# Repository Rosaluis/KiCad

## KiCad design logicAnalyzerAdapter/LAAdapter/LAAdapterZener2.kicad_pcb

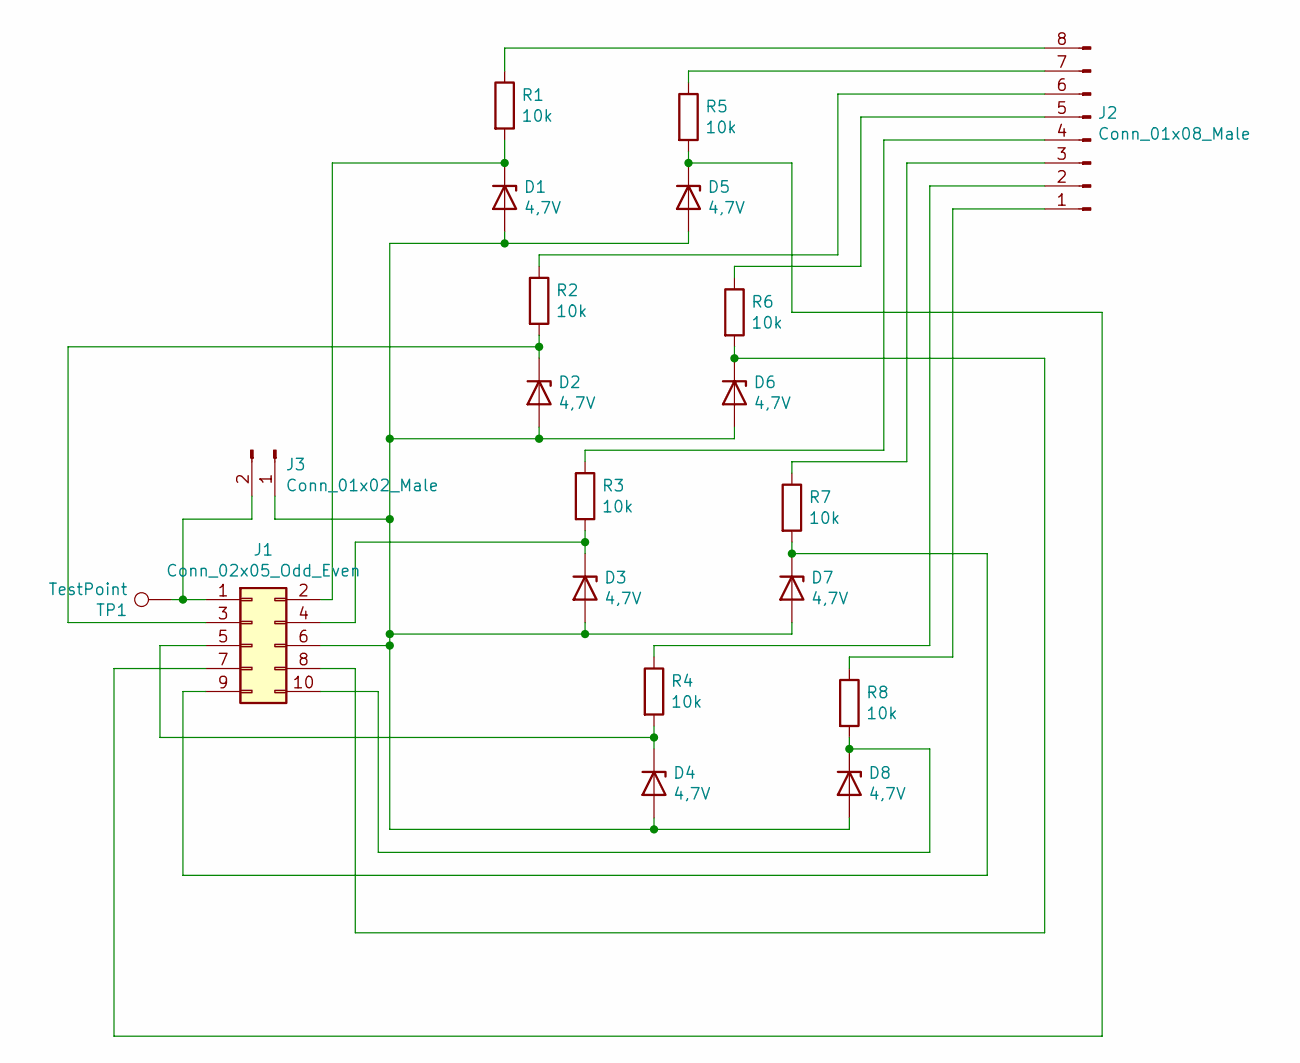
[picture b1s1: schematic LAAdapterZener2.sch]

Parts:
D1, D2, D3, D4, D5, D6, D7, D8: 4,7V; AR_D_DO-34_SOD68_P7.62mm_Horizontal
J1: Conn_02x05_Odd_Even; AR_PinHeader_2x05_P2.54mm_Horizontal_2
J2: Conn_01x08_Male; AR_PinHeader_1x08_P2.54mm_Vertical
J3: Conn_01x02_Male; SolderJumper-2_P1.3mm_Open_TrianglePad1.0x1.5mm
R1, R2, R3, R4, R5, R6, R7, R8: 10k; AR_R_0805_2012Metric
TP1: TestPoint; AR_PinHeader_1x01_P2.54mm_Vertical

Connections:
unnamed: D1.1 (K), J1.2, R1.2
unnamed: D1.2 (A), D2.2 (A), D3.2 (A), D4.2 (A), D5.2 (A), D6.2 (A), D7.2 (A), D8.2 (A), J1.6, J3.1
unnamed: D2.1 (K), J1.3, R2.2
unnamed: D3.1 (K), J1.4, R3.2
unnamed: D4.1 (K), J1.5, R4.2
unnamed: D5.1 (K), J1.7, R5.2
unnamed: D6.1 (K), J1.8, R6.2
unnamed: D7.1 (K), J1.9, R7.2
unnamed: D8.1 (K), J1.10, R8.2
unnamed: J1.1, J3.2, TP1.1
unnamed: J2.1, R8.1
unnamed: J2.2, R4.1
unnamed: J2.3, R7.1
unnamed: J2.4, R3.1
unnamed: J2.5, R6.1
unnamed: J2.6, R2.1
unnamed: J2.7, R5.1
unnamed: J2.8, R1.1

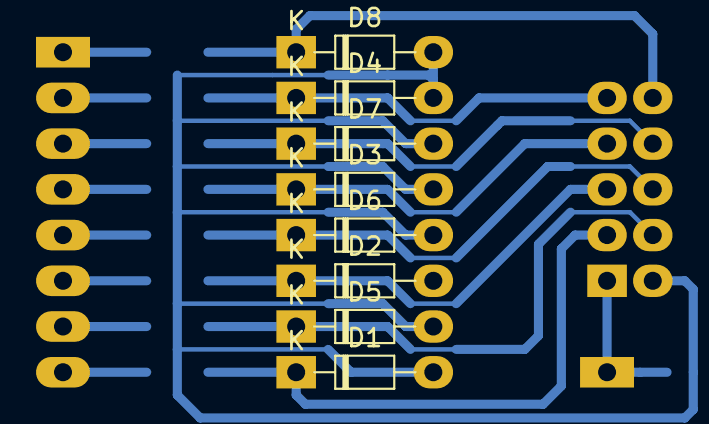
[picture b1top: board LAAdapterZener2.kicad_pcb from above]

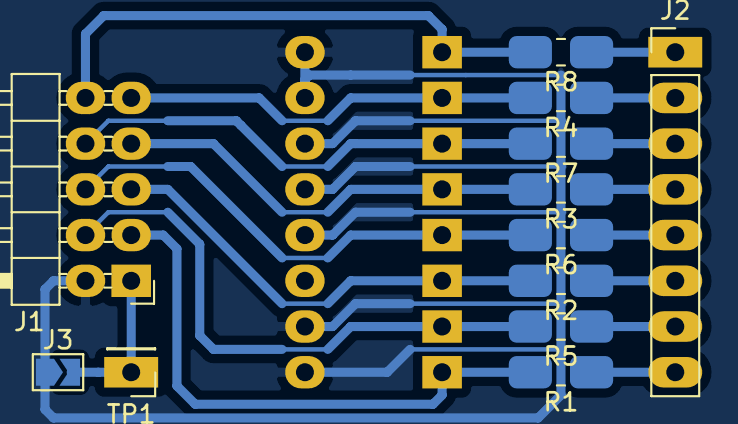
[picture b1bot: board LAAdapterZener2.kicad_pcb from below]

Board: 2 copper layers, 20 parts (12 on the bottom side), 18 nets.

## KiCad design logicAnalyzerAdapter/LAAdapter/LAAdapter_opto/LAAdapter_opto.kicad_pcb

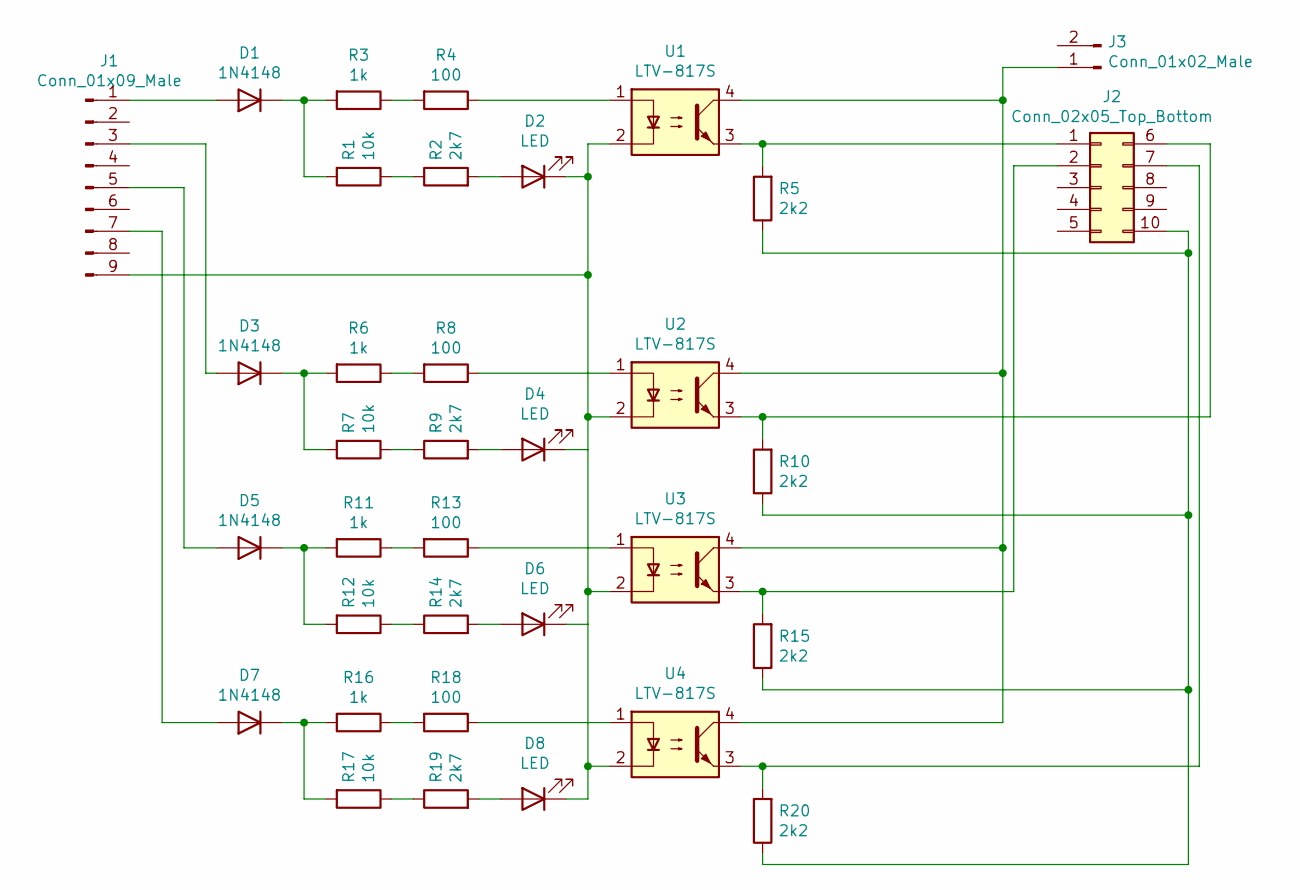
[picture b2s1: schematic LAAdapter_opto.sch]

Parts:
D1, D3, D5, D7: 1N4148; D_DO-35_SOD27_P7.62mm_Horizontal
D2, D4, D6, D8: LED; AR_LED_D3.0mm_2
J1: Conn_01x09_Male; AR_PinHeader_1x09_P2.54mm_Vertical
J2: Conn_02x05_Top_Bottom; AR_PinHeader_2x05_P2.54mm_Horizontal_2
J3: Conn_01x02_Male; AR_PinHeader_1x02_P2.54mm_Vertical
R1, R7, R12, R17: 10k; AR_R_0805_2012Metric
R2, R9, R14, R19: 2k7; AR_R_0805_2012Metric
R3, R6, R11, R16: 1k; AR_R_0805_2012Metric
R4, R8, R13, R18: 100; AR_R_0805_2012Metric
R5, R10, R15, R20: 2k2; AR_R_0805_2012Metric
U1, U2, U3, U4: LTV-817S; SMDIP-4_W9.53mm

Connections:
unnamed: D1.1 (K), R1.2, R3.2
unnamed: D1.2 (A), J1.1
unnamed: D2.1 (K), D4.1 (K), D6.1 (K), D8.1 (K), J1.9, U1.2, U2.2, U3.2, U4.2
unnamed: D2.2 (A), R2.2
unnamed: D3.1 (K), R6.2, R7.2
unnamed: D3.2 (A), J1.3
unnamed: D4.2 (A), R9.2
unnamed: D5.1 (K), R11.2, R12.2
unnamed: D5.2 (A), J1.5
unnamed: D6.2 (A), R14.2
unnamed: D7.1 (K), R16.2, R17.2
unnamed: D7.2 (A), J1.7
unnamed: D8.2 (A), R19.2
unnamed: J2.1, R5.2, U1.3
unnamed: J2.2, R15.2, U3.3
unnamed: J2.6, R10.2, U2.3
unnamed: J2.7, R20.2, U4.3
unnamed: J2.10, R5.1, R10.1, R15.1, R20.1
unnamed: J3.1, U1.4, U2.4, U3.4, U4.4
unnamed: R1.1, R2.1
unnamed: R3.1, R4.2
unnamed: R4.1, U1.1
unnamed: R6.1, R8.2
unnamed: R7.1, R9.1
unnamed: R8.1, U2.1
unnamed: R11.1, R13.2
unnamed: R12.1, R14.1
unnamed: R13.1, U3.1
unnamed: R16.1, R18.2
unnamed: R17.1, R19.1
unnamed: R18.1, U4.1

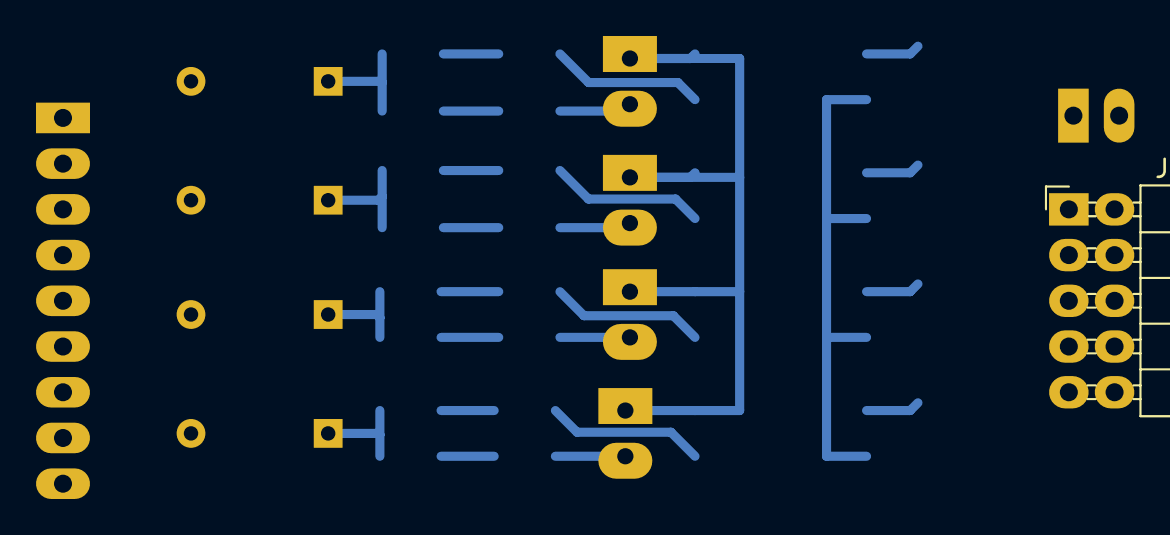
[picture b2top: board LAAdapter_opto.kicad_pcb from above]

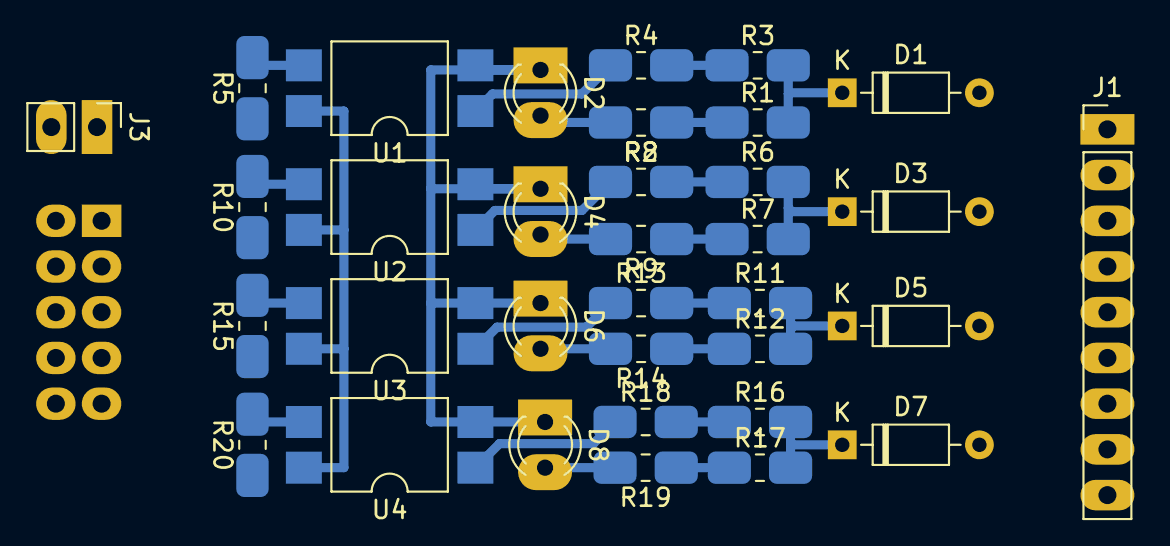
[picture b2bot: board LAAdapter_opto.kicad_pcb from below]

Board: 2 copper layers, 35 parts (34 on the bottom side), 31 nets.

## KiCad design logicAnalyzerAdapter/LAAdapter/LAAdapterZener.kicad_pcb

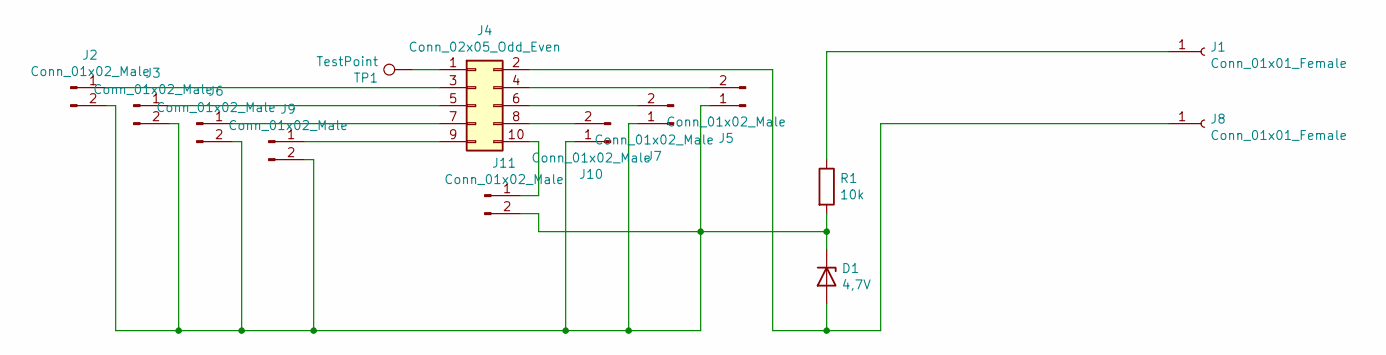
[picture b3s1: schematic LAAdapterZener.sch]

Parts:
D1: 4,7V; AR_D_DO-34_SOD68_P7.62mm_Horizontal
J1, J8: Conn_01x01_Female; AR_AMASS_4mm_Horizontal
J2, J3, J5, J6, J7, J9, J10, J11: Conn_01x02_Male; SolderJumper-2_P1.3mm_Open_Pad1.0x1.5mm
J4: Conn_02x05_Odd_Even; AR_PinHeader_2x05_P2.54mm_Horizontal
R1: 10k; AR_R_0805_2012Metric
TP1: TestPoint; AR_PinHeader_1x01_P2.54mm_Vertical

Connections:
unnamed: D1.1 (K), J2.2, J3.2, J5.1, J6.2, J7.1, J9.2, J10.1, J11.2, R1.2
unnamed: D1.2 (A), J4.2, J8.1
unnamed: J1.1, R1.1
unnamed: J2.1, J4.3
unnamed: J3.1, J4.5
unnamed: J4.1, TP1.1
unnamed: J4.4, J5.2
unnamed: J4.6, J7.2
unnamed: J4.7, J6.1
unnamed: J4.9, J9.1
unnamed: J4.8, J10.2
unnamed: J4.10, J11.1

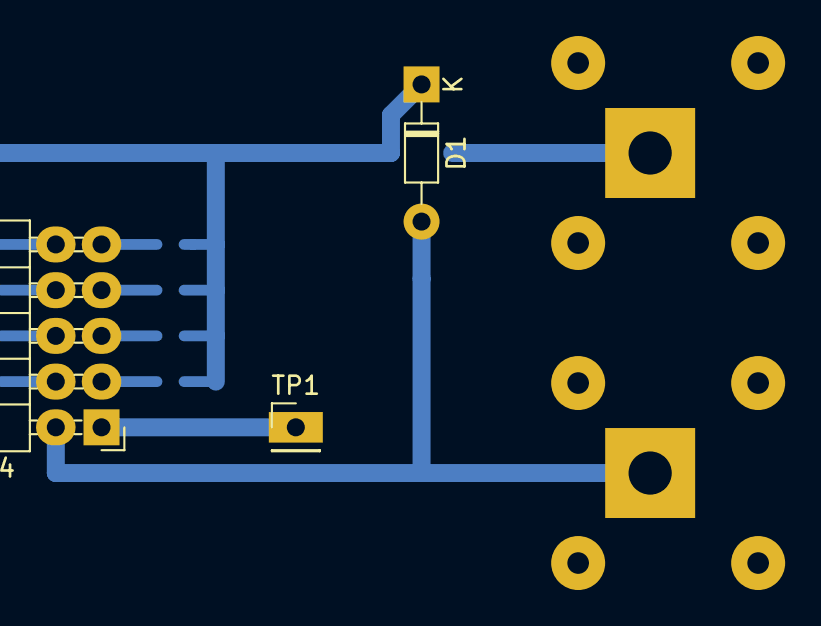
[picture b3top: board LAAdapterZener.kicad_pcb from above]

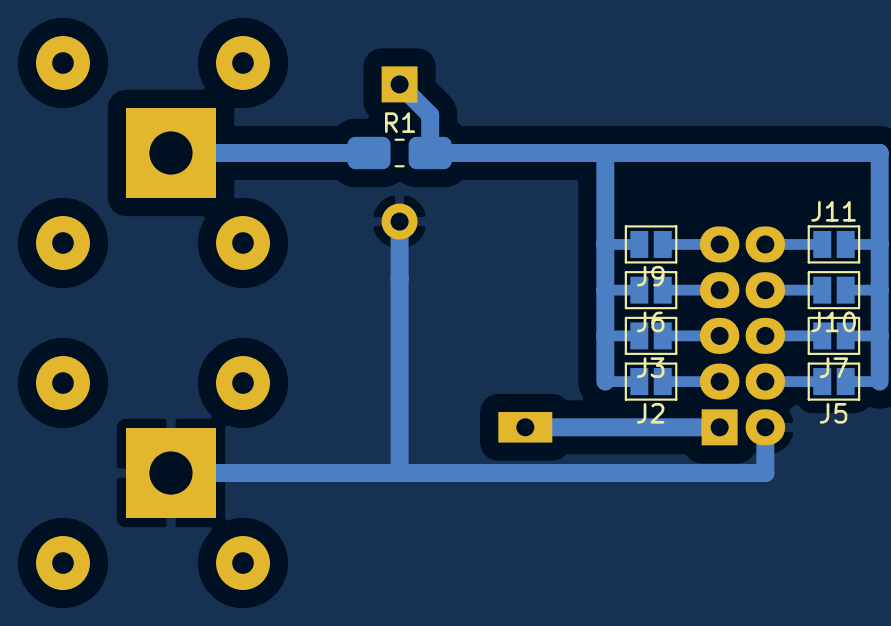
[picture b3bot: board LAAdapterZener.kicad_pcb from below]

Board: 2 copper layers, 14 parts (9 on the bottom side), 12 nets.

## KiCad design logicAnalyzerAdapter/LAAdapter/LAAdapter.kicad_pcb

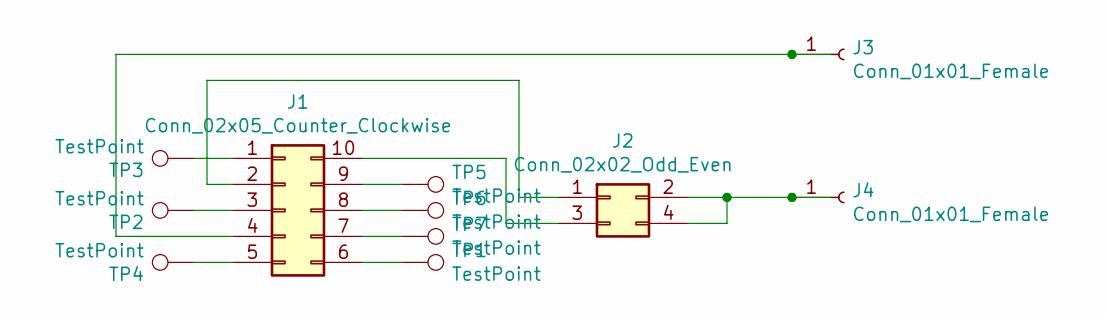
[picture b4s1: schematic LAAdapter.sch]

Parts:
J1: Conn_02x05_Counter_Clockwise; AR_PinHeader_2x05_P2.54mm_Horizontal
J2: Conn_02x02_Odd_Even; AR_PinHeader_2x02_P2.54mm_Vertical
J3, J4: Conn_01x01_Female; AR_AMASS_4mm_Horizontal
TP1, TP2, TP3, TP4, TP5, TP6, TP7: TestPoint; AR_PinHeader_1x01_P2.54mm_Vertical

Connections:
unnamed: J1.1, TP3.1
unnamed: J1.2, J2.1
unnamed: J1.3, TP2.1
unnamed: J1.4, J3.1
unnamed: J1.5, TP4.1
unnamed: J1.6, TP1.1
unnamed: J1.7, TP7.1
unnamed: J1.8, TP6.1
unnamed: J1.9, TP5.1
unnamed: J1.10, J2.3
unnamed: J2.2, J2.4, J4.1

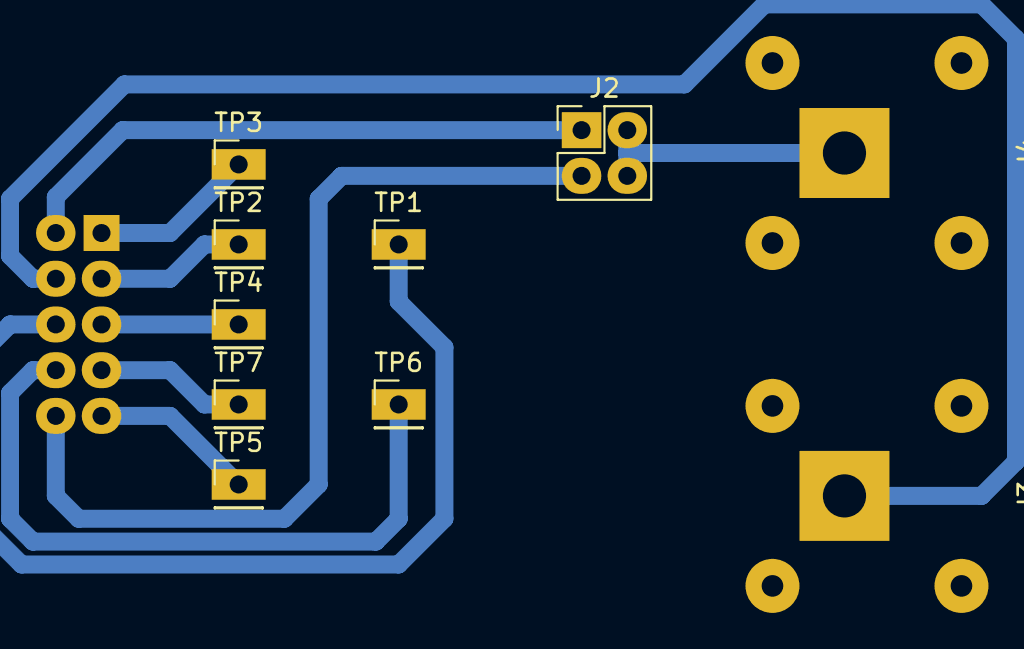
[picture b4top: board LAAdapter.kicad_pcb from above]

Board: 2 copper layers, 11 parts (1 on the bottom side), 11 nets.

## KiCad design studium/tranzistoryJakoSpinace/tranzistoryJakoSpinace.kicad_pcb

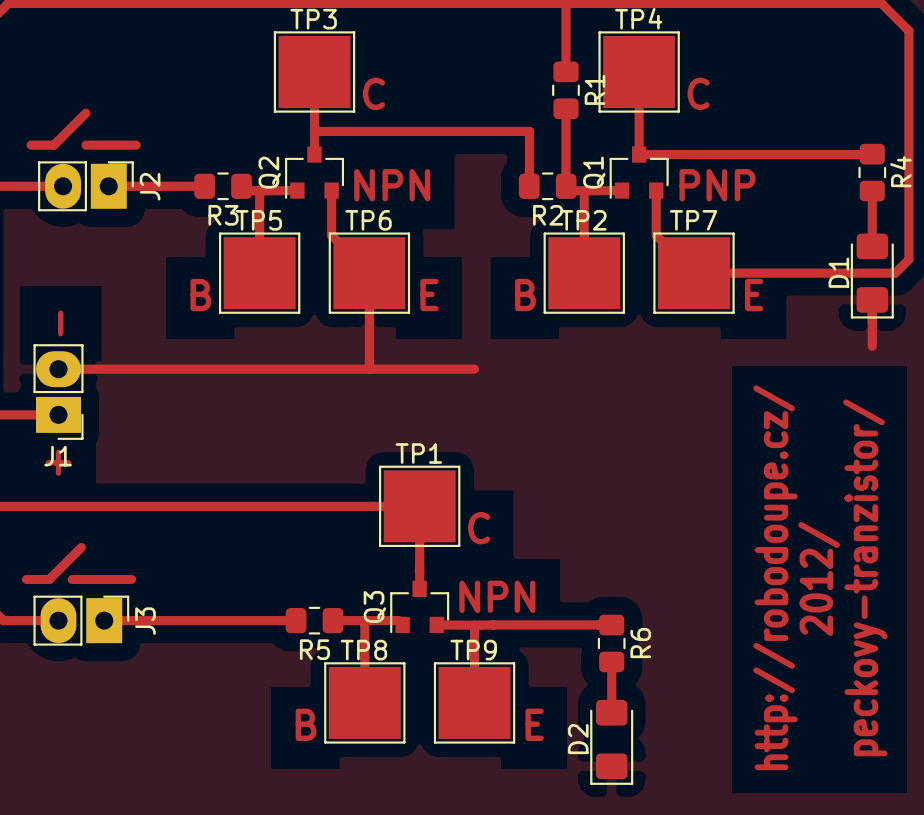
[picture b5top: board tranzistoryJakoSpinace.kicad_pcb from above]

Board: 2 copper layers, 23 parts (0 on the bottom side), 12 nets.

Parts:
D1, D2: LED; LED_1206_3216Metric_Pad1.42x1.75mm_HandSolder
J1, J2, J3: Conn_01x02_Male; AR_PinHeader_1x02_P2.54mm_Vertical
Q1: BC807; SOT-23
Q2, Q3: BC817; SOT-23
R1, R2, R3, R4, R5, R6: R; R_0805_2012Metric_Pad1.15x1.40mm_HandSolder
TP1, TP2, TP3, TP4, TP5, TP6, TP7, TP8, TP9: tp; TestPoint_Pad_4.0x4.0mm

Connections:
+12V: J1.1, J2.2, J3.2, Q1.2, Q3.3, R1.1, TP1.1, TP7.1
GND: D1.1, D2.1, J1.2, Q2.2, TP6.1
unnamed: D1.2, R4.2
unnamed: D2.2, R6.2
unnamed: J2.1, R3.2
unnamed: J3.1, R5.2
unnamed: Q1.1, R1.2, R2.1, TP2.1
unnamed: Q1.3, R4.1, TP4.1
unnamed: Q2.1, R3.1, TP5.1
unnamed: Q2.3, R2.2, TP3.1
unnamed: Q3.1, R5.1, TP8.1
unnamed: Q3.2, R6.1, TP9.1

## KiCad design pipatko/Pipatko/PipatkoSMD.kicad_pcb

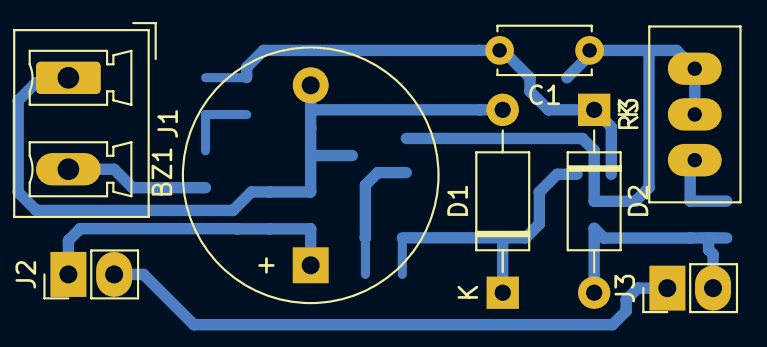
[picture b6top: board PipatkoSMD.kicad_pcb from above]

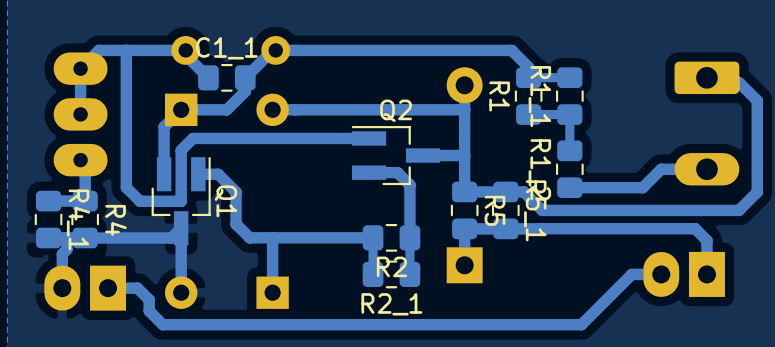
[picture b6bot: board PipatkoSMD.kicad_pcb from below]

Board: 2 copper layers, 20 parts (12 on the bottom side), 11 nets.

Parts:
BZ1: Buzzer; Buzzer_D14mm_H7mm_P10mm
C1: C; C_Disc_D5.0mm_W2.5mm_P5.00mm
C1_1: C; C_0805_2012Metric_Pad1.15x1.40mm_HandSolder
D1, D2: 1N4148; D_A-405_P10.16mm_Horizontal
J1: hroty; PhoenixContact_MCV_1,5_2-G-5.08_1x02_P5.08mm_Vertical
J2: vypinac; AR_PinHeader_1x02_P2.54mm_Vertical
J3: 9V= 1+ / 2-; AR_PinHeader_1x02_P2.54mm_Vertical
Q1: BC547; SOT-23_Handsoldering
Q2: BC557; SOT-23_Handsoldering
R1, R1_1, R1_2: 56k; R_0805_2012Metric_Pad1.15x1.40mm_HandSolder
R2, R2_1: 10k; R_0805_2012Metric_Pad1.15x1.40mm_HandSolder
R3: 2k5; AR_Potentiometer_Bourns_3296W_Vertical
R4, R4_1: 100R; R_0805_2012Metric_Pad1.15x1.40mm_HandSolder
R5, R5_1: 1k; R_0805_2012Metric_Pad1.15x1.40mm_HandSolder

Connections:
GND: D2.2, J3.2, Q1.3, R4.2, R4_1.2
unnamed: BZ1.1, J2.1, R5.2, R5_1.2
unnamed: BZ1.2, D1.2, J1.1, Q2.3, R5.1, R5_1.1
unnamed: C1.1, C1_1.1, Q2.1, R3.1, R3.2
unnamed: C1.2, C1_1.2, D2.1, Q1.2, R1.2, R1_1.2
unnamed: D1.1, Q1.1, R2.2, R2_1.2
unnamed: J1.2, R1_2.1
unnamed: J2.2, J3.1
unnamed: Q2.2, R2.1, R2_1.1
unnamed: R1.1, R1_1.1, R1_2.2
unnamed: R3.3, R4.1, R4_1.1

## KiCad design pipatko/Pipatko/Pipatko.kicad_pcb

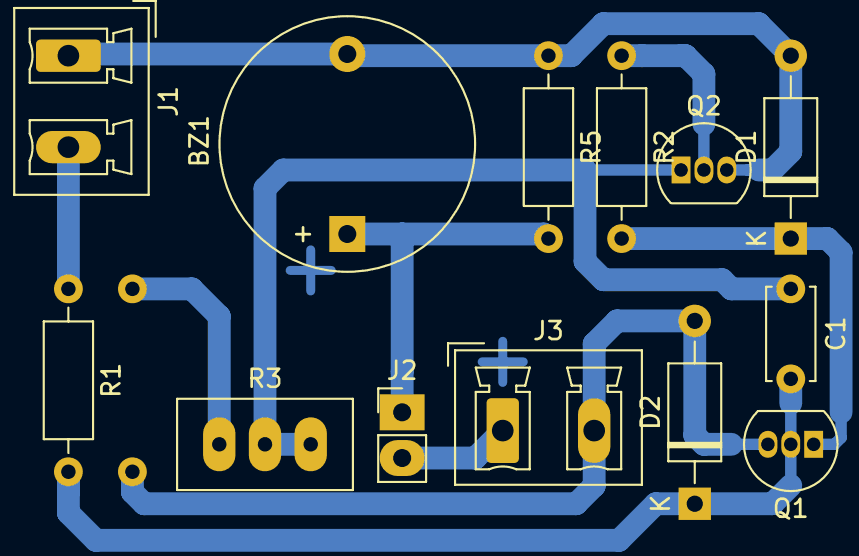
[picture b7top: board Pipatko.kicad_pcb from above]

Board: 2 copper layers, 14 parts (1 on the bottom side), 10 nets.

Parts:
BZ1: Buzzer; Buzzer_D14mm_H7mm_P10mm
C1: C; C_Disc_D5.0mm_W2.5mm_P5.00mm
D1, D2: 1N4148; D_A-405_P10.16mm_Horizontal
J1: hroty; PhoenixContact_MCV_1,5_2-G-5.08_1x02_P5.08mm_Vertical
J2: vypinac; AR_PinHeader_1x02_P2.54mm_Vertical
J3: 9V= 1+ / 2-; PhoenixContact_MCV_1,5_2-G-5.08_1x02_P5.08mm_Vertical
Q1: BC547; TO-92_Inline
Q2: BC557; TO-92_Inline
R1: 56k; R_Axial_DIN0207_L6.3mm_D2.5mm_P10.16mm_Horizontal
R2: 10k; R_Axial_DIN0207_L6.3mm_D2.5mm_P10.16mm_Horizontal
R3: 2k5; AR_Potentiometer_Bourns_3296W_Vertical
R4: 100R; R_Axial_DIN0207_L6.3mm_D2.5mm_P10.16mm_Horizontal
R5: 1k; R_Axial_DIN0207_L6.3mm_D2.5mm_P10.16mm_Horizontal

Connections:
GND: D2.2, J3.2, Q1.3, R4.2
unnamed: BZ1.1, J2.1, R5.2
unnamed: BZ1.2, D1.2, J1.1, Q2.3, R5.1
unnamed: C1.1, Q2.1, R3.1, R3.2
unnamed: C1.2, D2.1, Q1.2, R1.2
unnamed: D1.1, Q1.1, R2.2
unnamed: J1.2, R1.1
unnamed: J2.2, J3.1
unnamed: Q2.2, R2.1
unnamed: R3.3, R4.1

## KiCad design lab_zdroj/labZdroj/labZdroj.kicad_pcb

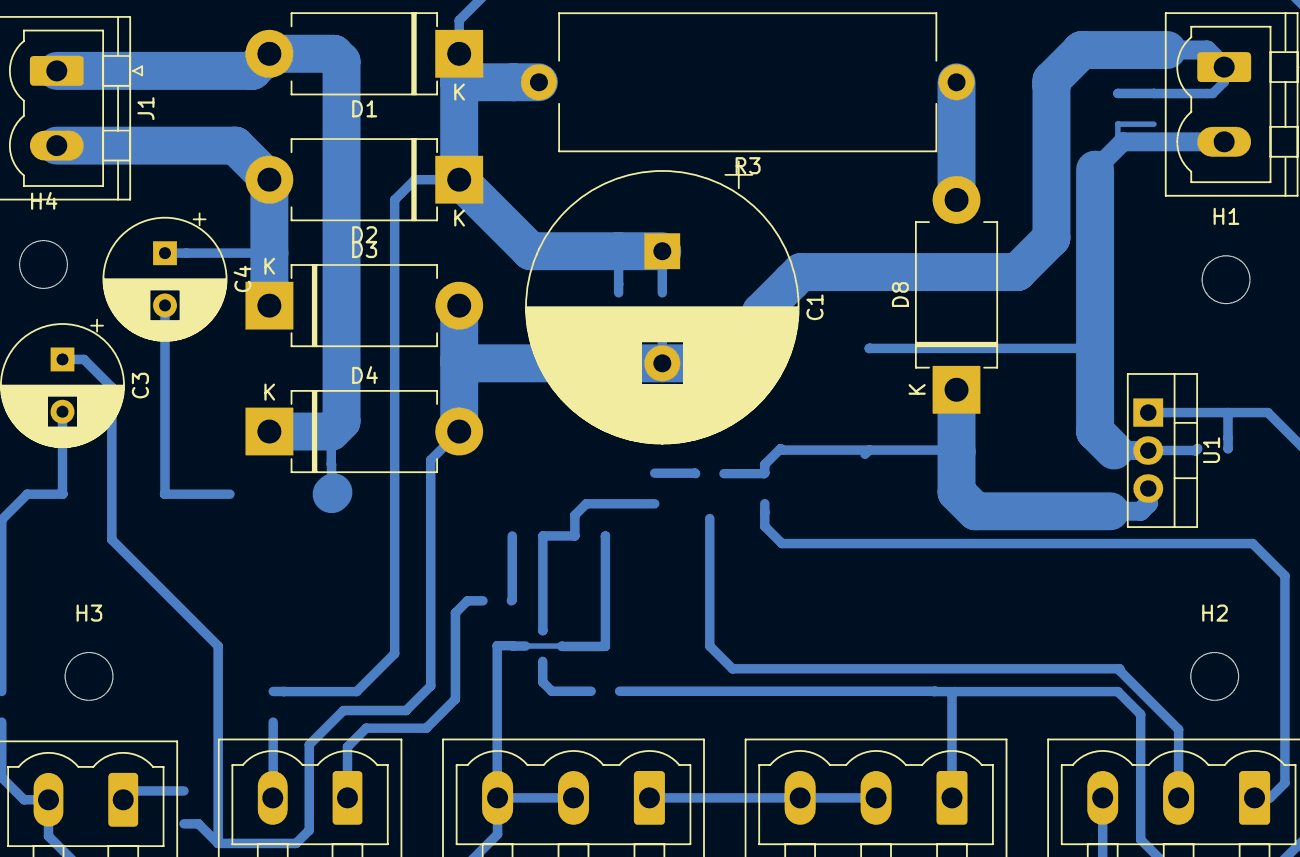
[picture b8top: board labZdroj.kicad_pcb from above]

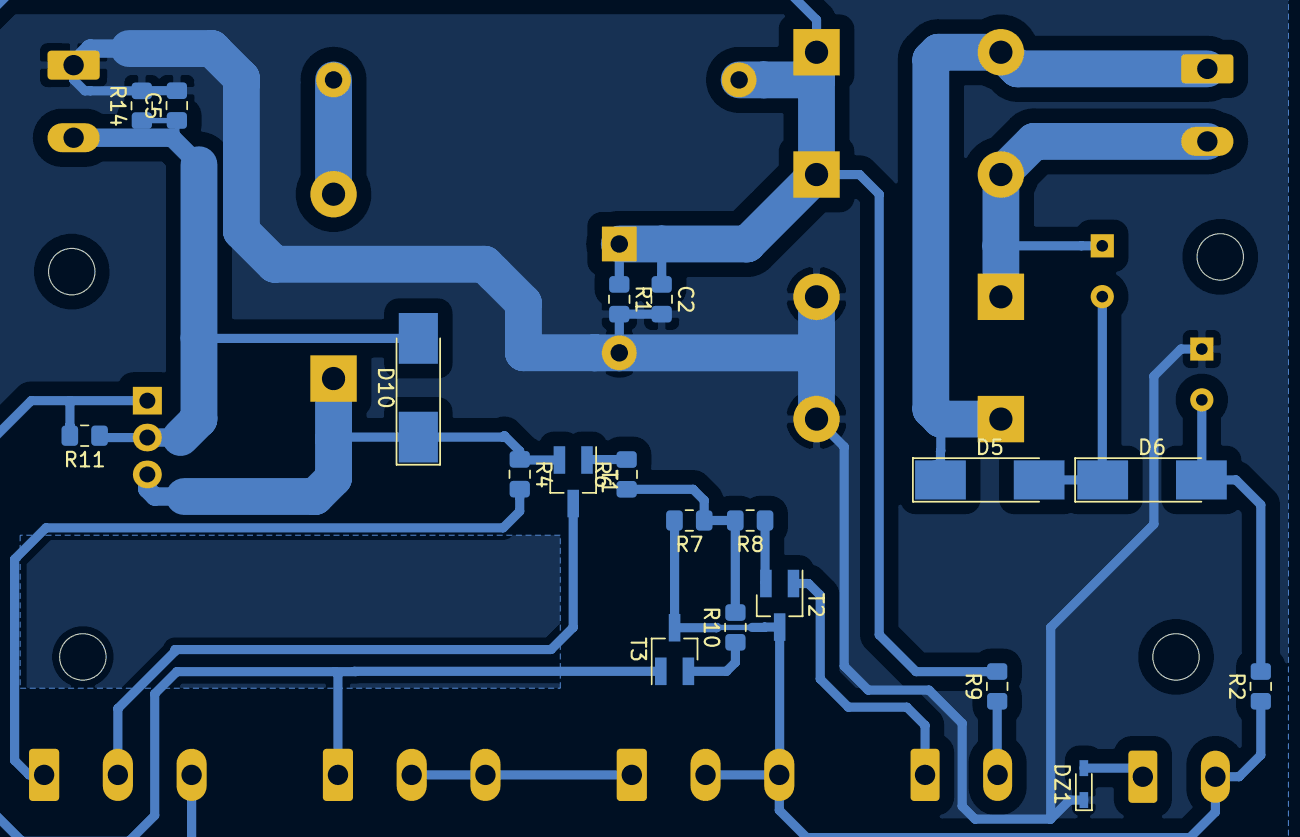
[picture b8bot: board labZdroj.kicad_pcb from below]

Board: 2 copper layers, 40 parts (19 on the bottom side), 21 nets.

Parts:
C1: 4m7; CP_Radial_D18.0mm_P7.50mm
C2, C5: 100n; C_0805_2012Metric_Pad1.15x1.40mm_HandSolder
C3, C4: 100u; CP_Radial_D8.0mm_P3.50mm
D1, D2, D3, D4, D8: BY550; D_DO-201AD_P12.70mm_Horizontal
D5, D6, D10: 1N4007; D_MELF_Handsoldering
DZ1: 4V1; D_SC-80_HandSoldering
H1, H2, H3, H4: MountingHole; MountingHole_3.2mm_M3
J1: 24V st; PhoenixContact_MSTBVA_2,5_2-G_1x02_P5.00mm_Vertical
J2: 0-30V ss; PhoenixContact_MSTBVA_2,5_2-G_1x02_P5.00mm_Vertical
J_D7: green_LED; PhoenixContact_MSTBVA_2,5_2-G_1x02_P5.00mm_Vertical
J_D9: red_LED; PhoenixContact_MSTBVA_2,5_2-G_1x02_P5.00mm_Vertical
J_R5: 1k; PhoenixContact_MSTBVA_2,5_3-G-5,08_1x03_P5.08mm_Vertical
J_R12: 100k; PhoenixContact_MSTBVA_2,5_3-G-5,08_1x03_P5.08mm_Vertical
J_R13: 5k; PhoenixContact_MSTBVA_2,5_3-G-5,08_1x03_P5.08mm_Vertical
R1, R2, R7: 2k7; R_0805_2012Metric_Pad1.15x1.40mm_HandSolder
R3: 0R27; R_Axial_Power_L25.0mm_W9.0mm_P27.94mm
R4: 680R; R_0805_2012Metric_Pad1.15x1.40mm_HandSolder
R6, R9: 30k; R_0805_2012Metric_Pad1.15x1.40mm_HandSolder
R8, R10: 220R; R_0805_2012Metric_Pad1.15x1.40mm_HandSolder
R11: 4k7; R_0805_2012Metric_Pad1.15x1.40mm_HandSolder
R14: 1k2; R_0805_2012Metric_Pad1.15x1.40mm_HandSolder
T1: BC327; SOT-23_Handsoldering
T2, T3: BC547; SOT-23_Handsoldering
U1: LM350_TO220; TO-220-3_Vertical

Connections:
+24V: C1.1, C2.1, D1.1, D2.1, J_R5.3, R1.1, R3.2, R9.2
GND: C1.2, C2.2, C3.1, C5.2, D3.2, D4.2, DZ1.1, J2.1, R1.2, R14.2
unnamed: C3.2, D6.2, R2.2
unnamed: C4.1, D2.2, D3.1, J1.2
unnamed: C4.2, D5.2, D6.1
unnamed: C5.1, D10.2, J2.2, R11.1, R14.1, U1.2
unnamed: D1.2, D4.1, D5.1, J1.1
unnamed: D8.2, R3.1
unnamed: D8.1, D10.1, R4.1, T1.2, U1.3
unnamed: DZ1.2, J_D7.1
unnamed: J_D7.2, J_R13.2, J_R13.3, R2.1, R7.2, T2.3, T3.3
unnamed: J_D9.1, T2.1
unnamed: J_D9.2, R9.1
unnamed: J_R5.1, R4.2
unnamed: J_R5.2, T1.3
unnamed: J_R12.1, R11.2, T3.1, U1.1
unnamed: J_R12.2, J_R12.3, J_R13.1
unnamed: R6.2, T1.1
unnamed: R8.1, T2.2
unnamed: R10.1, T3.2
unnamed: R6.1, R7.1, R8.2, R10.2

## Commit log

2020-12-05 První verze zazálohované desky na osvitovku a řízení vrtačky rámečků.
2020-12-05 Finální verze po OK CRC kontrole schématu.
2020-12-05 Upraveno schéma a první, nepříliš povedená verze PCB.
2020-12-06 Finální PCB k vytisknutí.
2020-12-06 Finálka pro výrobu.
2020-12-06 Nová, zmenšená verze.
2020-12-08 Úprava PCB pro jednostranný plošňák.
2020-12-08 Jednodušší řeření časování osvitové jednotky s NE555.
2020-12-08 další verze.
2020-12-13 Verze s mosfet tranzistorem se neosvědčila. Nahrazeno relátkem.
2020-12-13 Změna pouzder pro kondíky.
2020-12-13 Nový PCB.
2020-12-15 Měl jsem špatný pouzdro na relátku. Opraveno.
2020-12-17 finální verze pro výrobu č. 1
2020-12-18 sw pro arduino
2020-12-19 test a upgrade pcb.
2020-12-19 odkomentování seriové komunikace
2020-12-20 Totálně předělaný plošňák. Zvětšené plošky, širší cestičky. Založena vlastní knihovna.
2020-12-22 podklady pro nový a jednoduchý laboratorní zdroj na místo mého odpáleného.
2020-12-22 Přidán seznam součástek.
2020-12-22 Schéma dle internetu.
2020-12-22 Doplněno schéma, součástky importovány do PCB.
2020-12-23 Rozpracovaný pcb.
2020-12-24 pcb bez gnd plochy a všechny tři tranzistory jsou v smd provedení
2020-12-24 opravena chybějící cesta
2020-12-24 upgrade pcb, první finální verze.
2020-12-25 final pcb, předěláno na tranzistory v tht provedení.
2021-01-12 Akustická zkoušečka propojení. Schéma z AR08/2019.
2021-01-12 Drobné úpravy, přidán vypínač a testovací tlačítko.
2021-01-12 přiřazeny pouzdra součástek, otevření pcb.
2021-01-15 První verze PCB.
2021-01-16 ani nevím, zapomenutý upload...
2021-01-17 PCB verze s SMD součástkami.
2021-01-25 novinky.
2021-01-25 Stabilizátor do smd pouzdra.
2021-01-26 pár změn.
2021-01-26 skorofinální verze.
2021-01-26 finální verze.
2021-02-02 udělaná nová knihovna s názvem AR_Library. tester krokových motorků a taky A4988 modulů.
2021-03-14 nový projekt - adaptér k logickému analyzátoru
2021-03-14 prvni verze s PCB
2021-03-14 verze 2.0 s PCB, zjednodušená
2021-03-14 test krokových motorků
2021-03-14 update součástky v knihovně, update pcb
2021-03-16 Převodník logického analyzátoro se zenerkou pro U > 5V.
2021-03-16 Revert "Převodník logického analyzátoro se zenerkou pro U > 5V."
    This reverts commit 9bfffcb31ff9eddc9b28d3cd7f0cf31f5e37ab14.
2021-03-16 podlito mědí
2021-03-16 opravena hrubá chyba
2021-03-20 vícenásobná verze s optočleny
2021-03-20 nová zenerková verze pro všech 8 kanálů
2021-04-06 pro uplnost
2021-05-23 zesík
